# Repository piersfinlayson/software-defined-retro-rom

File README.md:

# One ROM

**One ROM To Rule Them All**

The most flexible ROM replacement for your retro computer. It is highly configurable and low-cost.  Get them fabbed at JLC for under $5 each in a quantity of 10 or more.

Based on a Raspberry Pi RP2350 or STM32F4 microcontroller.

One ROM emulates any system's 2364, 2332 and 2316 ROMs, with any chip select configuration, and can serve different images to multiple ROM sockets simultaneously.

Replaces failed ROMs in Commodore 64s, VIC-20s, PETs, disk drives.

One ROM was formerly known as Software Defined Retro ROM (SDRR).

## Key Features

💰 Based on sub-$2 microcontrollers.  [**Choose from Raspberry Pi or STM flavours**]((docs/MCU-SELECTION.md)).

⚡ **[Fast](docs/STM32-SELECTION.md)** enough for PETs, VIC-20s, C64s, 1541s, IEEE drives, etc. Support faster systems with higher end microcontroller.

📐 **[Same footprint](docs/images/sdrr-24-pin-side.png)** as original ROMs - doesn't overhang the socket like other solutions.

🚀 **[Quick programming](docs/PROGRAMMING.md)** - just connect 4 wires and `make run`. No programming jigs necessary.

🔌 **[Use a $5 programmer](docs/PI-PICO-PROGRAMMER.md)** - no expensive EEPROM programmer required.

🛠️ **[Reflash in situ](docs/PROGRAMMING.md)** - no need to remove the ROM from the host when reprogramming.

⚙️ **[Software configurable](docs/CONFIGURATION.md)** chip select lines - no hardware jumpers required.

💾 Stores up to **[16 ROM images](docs/STM32-SELECTION.md)** of different sizes and chip select configurations.  Image selectable via jumpers.

📦 **[Replace multiple ROMs with one ROM](docs/MULTI-ROM-SETS.md)** a single One ROM can replace up to 3 original ROMs e.g. all of C64 kernel, BASIC, character set.

🔀 **[Dynamic bank switching](docs/MULTI-ROM-SETS.md)** - switch between ROM images on the fly, e.g. different char ROMs.

💻 **[Hackable at runtime](docs/RUNTIME-ACCESS.md)** - change the ROM images being served and access telemetry from the ROM at runtime using **[Airfrog](https://piers.rocks/u/airfrog)** or other SWD probes.

🧩 **[Images combined automatically](docs/CONFIGURATION.md)** - no need to manually build up your own larger PROM image containing multiple retro ROMs.

🏭 **[Two layer PCB](sdrr-pcb/README.md)**, component on single-side, limited BOM for low manufacturing cost/complexity.

🎯 Supports multiple **[STM32F4xxR](docs/STM32-SELECTION.md)** variants: F401, F411, F405, F446 (others can be added).

🔓 **[Open source](LICENSE.md)** software and hardware.

## Introduction

The video below provides an introduction to One ROM:

## Hardware

This is the RP2350 24-pin version, hardware revison A.  See [sdrr-pcb](sdrr-pcb/README.md) for the hardware designs and documentation.

<div style="display: flex; justify-content: center; gap: 20px;">
  
</div>

## Quick Start

You have two options

- [use the pre-built binaries](#pre-built-binaries)
- [build the firmware yourself.](#build-yourself)

### Pre-built Binaries

Use [Airfrog](https://piers.rocks/u/airfrog) or your favourite STM32 programmer to flash the pre-built binaries from the project's [releases](https://github.com/piersfinlayson/software-defined-retro-rom/releases/) page.  Scroll down to the "Assets" section of the latest release, and download the `bin-*.zip` or `elf-*.zip` file for your STM32 variant.  These zip files contain pre-built binaries for the various One ROM image collections, including the C64, VIC-20, PET, and 1541 disk drive.

### Build Yourself

Once you have the project cloned, and the required [dependencies](INSTALL.md) installed, you can build and flash an One ROM image using the following commands - replace `f411re` with your [target MCU variant](docs/MCU-SELECTION.md), and [`config/c64.mk`](/config/c64.mk) with the [configuration](config/README.md#available-configurations) you want to use.

```bash
# C64 using RP2350
HW_REV=p24-a MCU=rp2350 CONFIG=config/c64.mk make run
```

```bash
# C64 using F411RE
MCU=f411re CONFIG=config/c64.mk make run
```

```bash
# VIC-20 (PAL) using F411RE
MCU=f411re CONFIG=config/vic20-pal.mk make run
```

```bash
# PET 40 column 50Hz using F411RE
MCU=f411re CONFIG=config/pet-4-40-50.mk make run
```

This will download the desired ROM images automatically, generate the required firmware, and flash it to One ROM.

### After Flashing

Set the [One ROM jumpers](docs/IMAGE-SELECTION.md) to select the desired ROM image (see the [config file](/config/), or logs from your One ROM device, for which # corresponds to which image) and you're now ready to install the One ROM device in your retro system.

For configuration options, see [Configuration](docs/CONFIGURATION.md) and the [Makefile](Makefile).

## Documentation

| Topic | Description |
|-------|-------------|
| [Frequently Asked Questions](docs/FAQ.md) | Answers to common questions about One ROM. |
| [Installation](INSTALL.md) | Installation of dependencies. |
| [Programming](docs/PROGRAMMING.md) | How to program One ROM. |
| [Available Configurations](config/README.md#available-configurations) | Various pre-collated ROM collection configurations. |
| [MCU Selection](docs/MCU-SELECTION.md) | How to select the appropriate MCU for your application. |
| [Image Selection](docs/IMAGE-SELECTION.md) | How to tell One ROM which of the installed ROM images to serve. |
| [Image Sets](docs/MULTI-ROM-SETS.md) | How to use a single One ROM to support multiple ROMs simultaneously or to dynamically switch between images. |
| [Configuration](docs/CONFIGURATION.md) | One ROM configuration options. |
| [Runtime Access/Control](docs/RUNTIME-ACCESS.md) | Access and control the One ROM while it is serving ROMs. |
| [Compatibility](docs/COMPATIBILITY.md) | Compatibility with various retro systems. |
| [Logging](docs/LOGGING.md) | How to enable and use One ROM logging. |
| [Technical Summary](docs/TECHNICAL-SUMMARY.md) | Overview of the One ROM architecture, operation and design decisions. |
| [Technical Details](docs/TECHNICAL-DETAILS.md) | Technical details of the One ROM firmware and hardware. |
| [Custom Hardware](docs/CUSTOM-HARDWARE.md) | Guide on designing custom hardware for One ROM. |
| [Build System](docs/BUILD-SYSTEM.md) | How the One ROM build system works. |
| [Voltage Levels](docs/VOLTAGE-LEVELS.md) | How the One ROM supports the required logic voltage levels. |
| [Pi Pico Programmer](docs/PI-PICO-PROGRAMMER.md) | How to use a $5 Raspberry Pi Pico as a programmer for One ROM. |
| [Manufacturing Test](docs/MANUFACTURING-TEST.md) | Information on testing One ROM during manufacturing. |
| [STM32 Clones](docs/STM32-CLONES.md) | Information using STM32 clones with One ROM. |
| [Future Enhancements](docs/FUTURE-ENHANCEMENTS.md) | Possible future enhancements under consideration. |
| [License](LICENSE.md) | One ROM software and hardware licenses. |

## Debugging

The best place to start with debugging is [`Logging`](docs/LOGGING.md).  This will help you see what the One ROM is doing, and why it may not be working as expected.

If you have an [Airfrog](https://piers.rocks/u/airfrog), you can use it to inspect the One ROM firmware and its current state.

If you'd like a hand, raise an issue on the [GitHub issues page](https://github.com/piersfinlayson/software-defined-retro-rom/issues).  Please provide:

- the MCU you are using and the PCB type/revision
- the retro system you are trying to One ROM with
- any logging from One ROM
- ideally, the firmware image, if you are happy to share.

If you have built the firmware yourself, rather than using a pre-built release image, also provide:

- your build configuration
- the output from `make info-detail`.

## License

See [LICENSE](LICENSE.md) for software and hardware licensing information.

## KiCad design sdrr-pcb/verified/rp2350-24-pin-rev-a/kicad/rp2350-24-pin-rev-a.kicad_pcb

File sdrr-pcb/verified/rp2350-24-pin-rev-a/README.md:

# RP2350 24 Pin Rev A

23xx (RP2350 24 pin) ROM replacement SDRR PCB.

**Verified** - The BOM/CPL files have been verified using JLCPCB.  However, you should always check the gerbers, component lists and component orientations with your supplier before ordering.

This is the first RP2350 revision, supported by v0.4.0 of the firmware.  While testing of all main features has been performed, this hardware design is less mature than the STM32F4 designs.

<div style="text-align: center;">
  
</div>

## Contents

- [Schematic](one-rom-24-pin-rp2350-rev-a-schematic.pdf)
- [Fab Notes](one-rom-24-pin-rp2350-rev-a-fab-notes.pdf)
- [Fab Files](fab/)
- [KiCad Design Files](kicad/)
- [Errata](#errata)
- [Notes](#notes)
- [Changelog](#changelog)

## Errata

None

## Notes

None

## Changelog

First revison

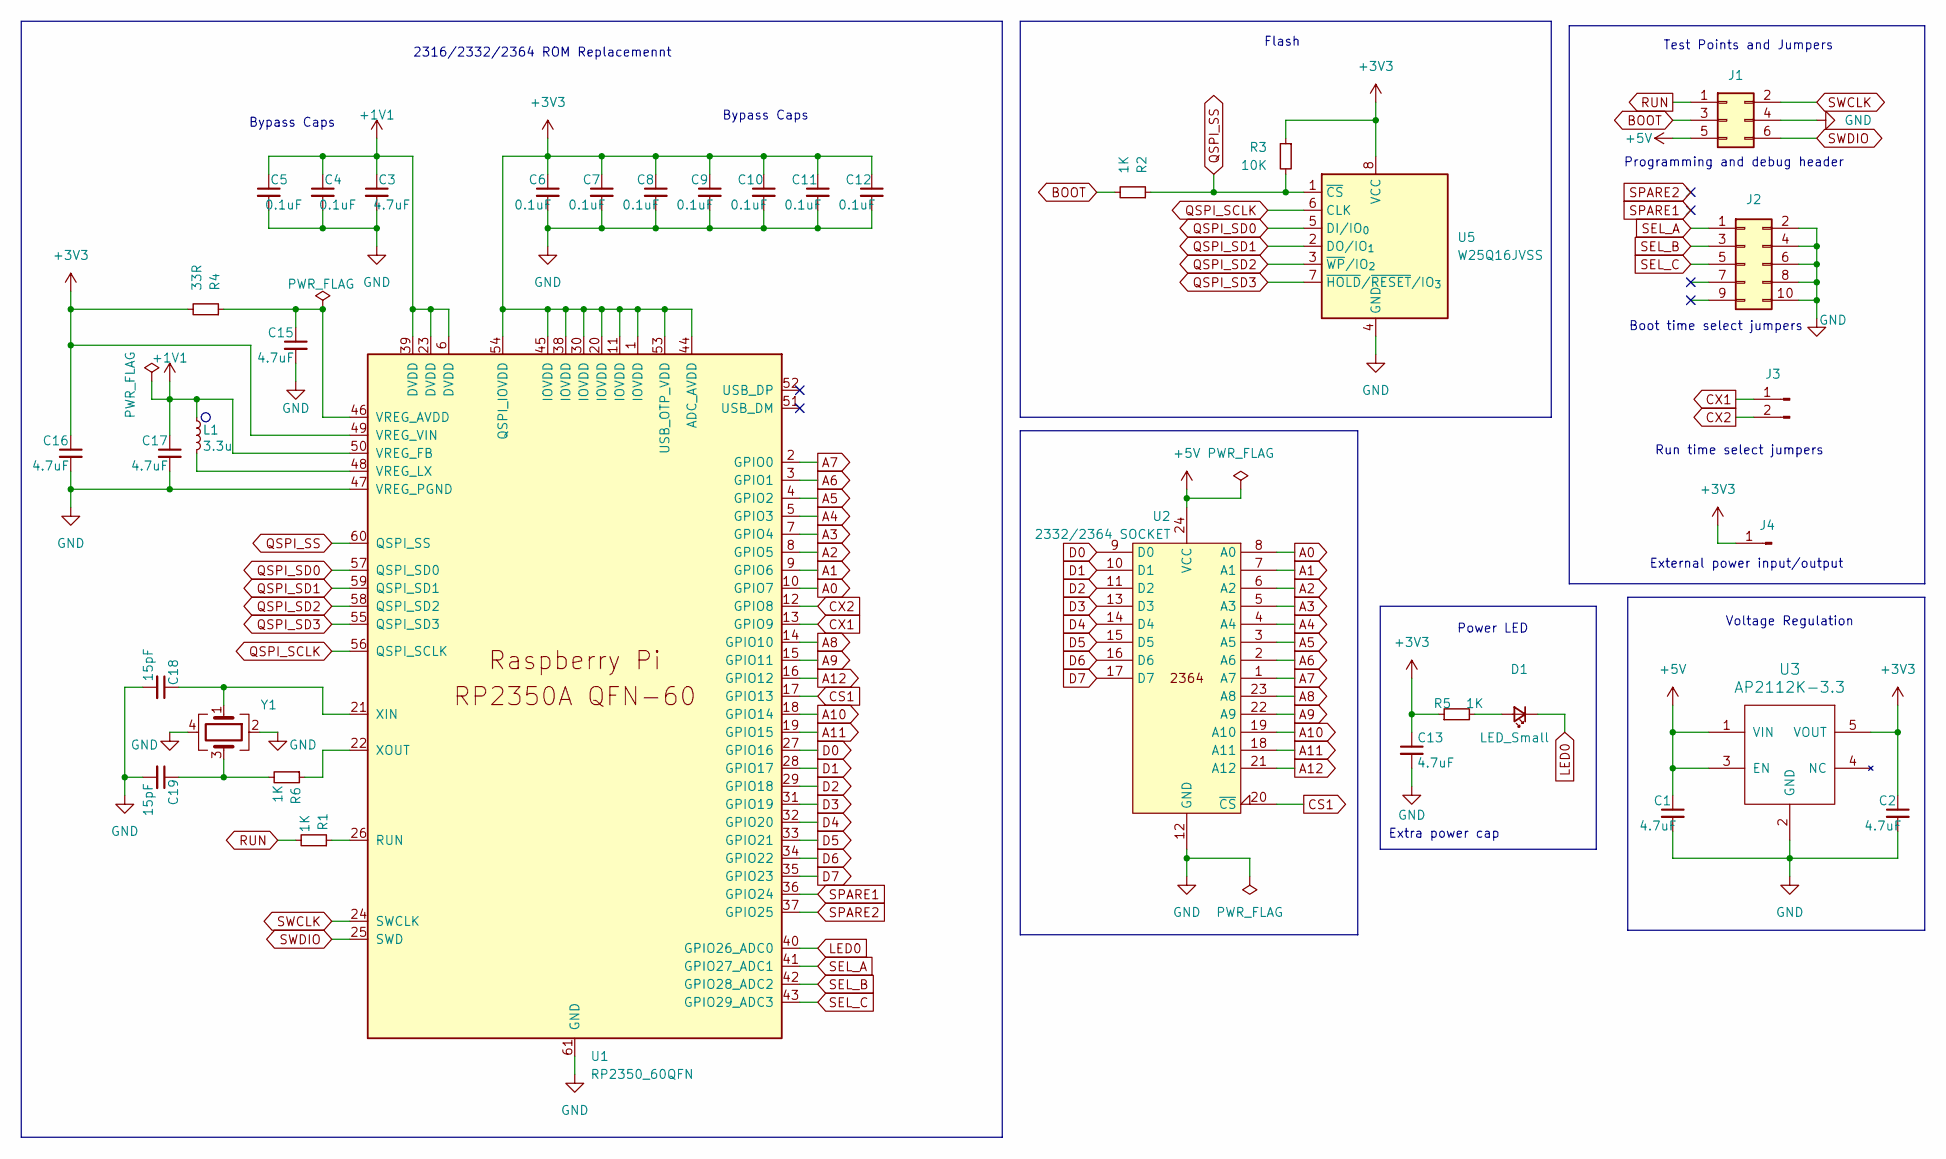
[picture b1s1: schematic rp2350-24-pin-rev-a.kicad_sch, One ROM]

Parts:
C1, C2, C3, C13, C15: 4.7uF; C_0402_1005Metric; LCSC C23733
C4, C5, C6, C7, C8, C9, C10, C11, C12: 0.1uF; C_0402_1005Metric; LCSC C1525
C16, C17: 4.7uF; C_0402_1005Metric_small_pads; LCSC C23733
C18, C19: 15pF; C_0402_1005Metric; LCSC C1548
D1: LED_Small; LED_0603_1608Metric; LCSC C2286
J1: Conn_02x03_Odd_Even; PinHeader_2x03_P2.54mm_Vertical
J2: Conn_02x05_Odd_Even; PinHeader_2x05_P2.54mm_Vertical custom silkscreen
J3: Conn_01x02_Pin; PinHeader_1x02_P2.54mm_Vertical
J4: Conn_01x01_Pin; PinHeader_1x01_P2.54mm_Vertical
L1: 3.3u; L_pol_2016; LCSC C42411119
R1, R2, R5, R6: 1K; R_0402_1005Metric; LCSC C11702
R3: 10K; R_0402_1005Metric; LCSC C25744
R4: 33R; R_0402_1005Metric; LCSC C25105
U1: RP2350_60QFN; RP2350-QFN-60-1EP_7x7_P0.4mm_EP3.4x3.4mm_ThermalVias; LCSC C42411118
U2: 2332/2364 SOCKET; 2x12 dip pin output 600mil centres no ss
U3: AP2112K-3.3; SOT-23-5; LCSC C51118
U5: W25Q16JVSS; Winbond_USON-8-1EP_3x2mm_P0.5mm_EP0.2x1.6mm; LCSC C2843335
Y1: Crystal_GND24; Crystal_SMD_Abracon_ABM8G-4Pin_3.2x2.5mm; LCSC C20625731

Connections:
+1V1: C3.1, C4.1, C5.1, C17.1, L1.1, U1.6 (DVDD), U1.23 (DVDD), U1.39 (DVDD), U1.50 (VREG_FB)
+3V3: C2.1, C6.1, C7.1, C8.1, C9.1, C10.1, C11.1, C12.1, C13.1, C16.1, J4.1, R3.1, R4.2, R5.1, U1.1 (IOVDD), U1.11 (IOVDD), U1.20 (IOVDD), U1.30 (IOVDD), U1.38 (IOVDD), U1.44 (ADC_AVDD), U1.45 (IOVDD), U1.49 (VREG_VIN), U1.53 (USB_OTP_VDD), U1.54 (QSPI_IOVDD), U3.5 (VOUT), U5.8 (VCC)
+5V: C1.1, J1.5, U2.24 (VCC), U3.1 (VIN), U3.3 (EN)
A0: U1.10 (GPIO7), U2.8 (A0)
A1: U1.9 (GPIO6), U2.7 (A1)
A2: U1.8 (GPIO5), U2.6 (A2)
A3: U1.7 (GPIO4), U2.5 (A3)
A4: U1.5 (GPIO3), U2.4 (A4)
A5: U1.4 (GPIO2), U2.3 (A5)
A6: U1.3 (GPIO1), U2.2 (A6)
A7: U1.2 (GPIO0), U2.1 (A7)
A8: U1.14 (GPIO10), U2.23 (A8)
A9: U1.15 (GPIO11), U2.22 (A9)
A10: U1.18 (GPIO14), U2.19 (A10)
A11: U1.19 (GPIO15), U2.18 (A11)
A12: U1.16 (GPIO12), U2.21 (A12)
BOOT: J1.3, R2.2
CS1: U1.17 (GPIO13), U2.20 (~CS)
CX1: J3.1, U1.13 (GPIO9)
CX2: J3.2, U1.12 (GPIO8)
D0: U1.27 (GPIO16), U2.9 (D0)
D1: U1.28 (GPIO17), U2.10 (D1)
D2: U1.29 (GPIO18), U2.11 (D2)
D3: U1.31 (GPIO19), U2.13 (D3)
D4: U1.32 (GPIO20), U2.14 (D4)
D5: U1.33 (GPIO21), U2.15 (D5)
D6: U1.34 (GPIO22), U2.16 (D6)
D7: U1.35 (GPIO23), U2.17 (D7)
GND: C1.2, C2.2, C3.2, C4.2, C5.2, C6.2, C7.2, C8.2, C9.2, C10.2, C11.2, C12.2, C13.2, C15.2, C16.2, C17.2, C18.2, C19.2, J1.4, J2.2, J2.4, J2.6, J2.8, J2.10, U1.47 (VREG_PGND), U1.61 (GND), U2.12 (GND), U3.2 (GND), U5.4 (GND), Y1.2, Y1.4
LED0: D1.1 (K), U1.40 (GPIO26_ADC0)
unnamed: C19.1, R6.2, Y1.3
unnamed: D1.2 (A), R5.2
unnamed: R1.1, U1.26 (RUN)
unnamed: C15.1, R4.1, U1.46 (VREG_AVDD)
unnamed: L1.2, U1.48 (VREG_LX)
unnamed: C18.1, U1.21 (XIN), Y1.1
unnamed: R6.1, U1.22 (XOUT)
QSPI_SCLK: U1.56 (QSPI_SCLK), U5.6 (CLK)
QSPI_SD0: U1.57 (QSPI_SD0), U5.5 (DI/IO_{0})
QSPI_SD1: U1.59 (QSPI_SD1), U5.2 (DO/IO_{1})
QSPI_SD2: U1.58 (QSPI_SD2), U5.3 (~WP/IO_{2})
QSPI_SD3: U1.55 (QSPI_SD3), U5.7 (~HOLD/~RESET/IO_{3})
QSPI_SS: R2.1, R3.2, U1.60 (QSPI_SS), U5.1 (~CS)
RUN: J1.1, R1.2
SEL_A: J2.1, U1.41 (GPIO27_ADC1)
SEL_B: J2.3, U1.42 (GPIO28_ADC2)
SEL_C: J2.5, U1.43 (GPIO29_ADC3)
SPARE1: U1.36 (GPIO24)
SPARE2: U1.37 (GPIO25)
SWCLK: J1.2, U1.24 (SWCLK)
SWDIO: J1.6, U1.25 (SWD)

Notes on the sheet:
Run time select jumpers
Voltage Regulation
Extra power cap
2316/2332/2364 ROM Replacemennt
Bypass Caps
Power LED
Programming and debug header
External power input/output
Flash
Boot time select jumpers
Test Points and Jumpers

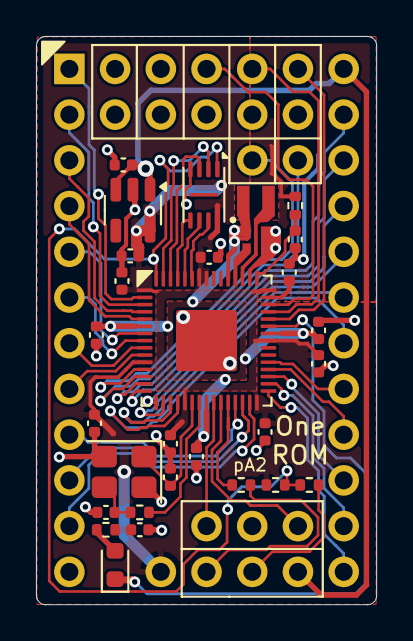
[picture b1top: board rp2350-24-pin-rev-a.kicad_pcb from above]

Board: 2 copper layers, 18.9 x 31.6 mm, 35 parts (0 on the bottom side), 49 nets.

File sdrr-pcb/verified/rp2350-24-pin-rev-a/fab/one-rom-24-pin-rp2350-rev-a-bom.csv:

"Reference","Value","Qty","DNP","LCSC","Comment","Price(10)"
"C1,C2,C3,C13,C15,C16,C17","4.7uF","7","","C23733","Samsung Electro-Mechanics CL05A475MP5NRNC","$0.0048"
"C4,C5,C6,C7,C8,C9,C10,C11,C12","0.1uF","9","","C1525","Samsung Electro-Mechanics CL05B104KO5NNNC","$0.0011"
"C18,C19","15pF","2","","C1548","FH (Guangdong Fenghua Advanced Tech) 0402CG150J500NT","$0.0010"
"D1","LED_Small","1","","C2286","Hubei KENTO Elec KT-0603R","$0.0056"
"L1","3.3u","1","","C42411119","Abracon LLC AOTA-B201610S3R3-101-T","$0.2736"
"R1,R2,R5,R6","1K","4","","C11702","UNI-ROYAL(Uniroyal Elec) 0402WGF1001TCE","$0.0005"
"R3","10K","1","","C25744","UNI-ROYAL(Uniroyal Elec) 0402WGF1002TCE","$0.0005"
"R4","33R","1","","C25105","UNI-ROYAL(Uniroyal Elec) 0402WGF330JTCE","$0.0006"
"U1","RP2350_60QFN","1","","C42411118","Raspberry Pi RP2350A","$1.4430"
"U3","AP2112K-3.3","1","","C51118","Diodes Incorporated AP2112K-3.3TRG1","$0.1059"
"U5","W25Q16JVSS","1","","C2843335","Winbond Elec W25Q16JVUXIQ","$0.5220"
"Y1","Crystal_GND24","1","","C20625731","Abracon LLC ABM8-272-T3","$0.4200"

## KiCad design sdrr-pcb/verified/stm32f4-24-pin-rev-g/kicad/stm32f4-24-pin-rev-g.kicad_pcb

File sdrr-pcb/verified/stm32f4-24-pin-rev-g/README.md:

# STM32F4 24 Pin Rev G

One ROM 23xx (STM32F4 24 pin) ROM replacement PCB.

**Partially Verified**: Has been verified with STM32F411.  Has not been verified with STM32F405 (although electrically very similar to rev F so highly likely to work).

Electrically similar to the [STM32F4 24 Pin Rev F2](../../verified/stm32f4-24-pin-rev-f2/README.md) board, but with some minor changes to layout:
- A new 2x3 programming header is on the bottom of the PCB - between pins 12 and 13.  This provides compatibility with the 1x3 SWD header on the Pico/Pico 2s.
  - As part of this BOOT0 has been moved to this header.
- A 5th image select jumper has been added to the top of the PCB, in plact of BOOT0. It is expected that this wil be used for other purposes other than image selection - such as host reset line, driven by an attached co-processor, such as Airfrog.
- The 5 image select jumpers have been relaballed A-E, and in the reverse order to the F2 board - with the intent that the least significant bit is now on the right.
- Closing the jumpers now pulls the image select line low, rather than high.  This is to expose GND rather than 3V3 on the unconnected pin, which is safer.
- An additional 3V3 and GND pair of pins has been added below X1/X2.  This can be used to power the board for progamming, instead of 5V on the programming header, or to tap a 3V3 source from the on-board regulator.  Care should be taken not to overload this.
- An additional single 3V3 pin has been added to the left of the programming header, for similar reasons.
- The MCO1 (optional clock output) test point has been moved to the underside of the PCB, and is now labelled TP1.
- The status LED has been moved to to next to the programming header, to avoid a daughterboard obscuring it.
- Moved to 0402 passives, with the expectation that most people will use an assembly service, and with a microscope and a decent iron, 0402 is also hand solderable.

There is a single set of gerbers, one CPL/POS file and multiple BOM files, one for each of the followingF4xx microcontrollers, in ascending order of cost:
- STM32F401RET6
- STM32F411RET6
- GD32F405RGT6
- STM32F405RGT6
- STM32F446RET6

<div style="text-align: center;">
  
</div>

## Contents

- [Schematic](sdrr-24-pin-rev-g1-schematic.pdf)
- [Fab Files](fab/) - unverified
- [KiCad Design Files](kicad/)
- [Errata](#errata)
- [Notes](#notes)
- [Changelog](#changelog)
- [BOM](#bom)

## Errata

## Notes

## Changelog

See above

## BOM

See fab files.

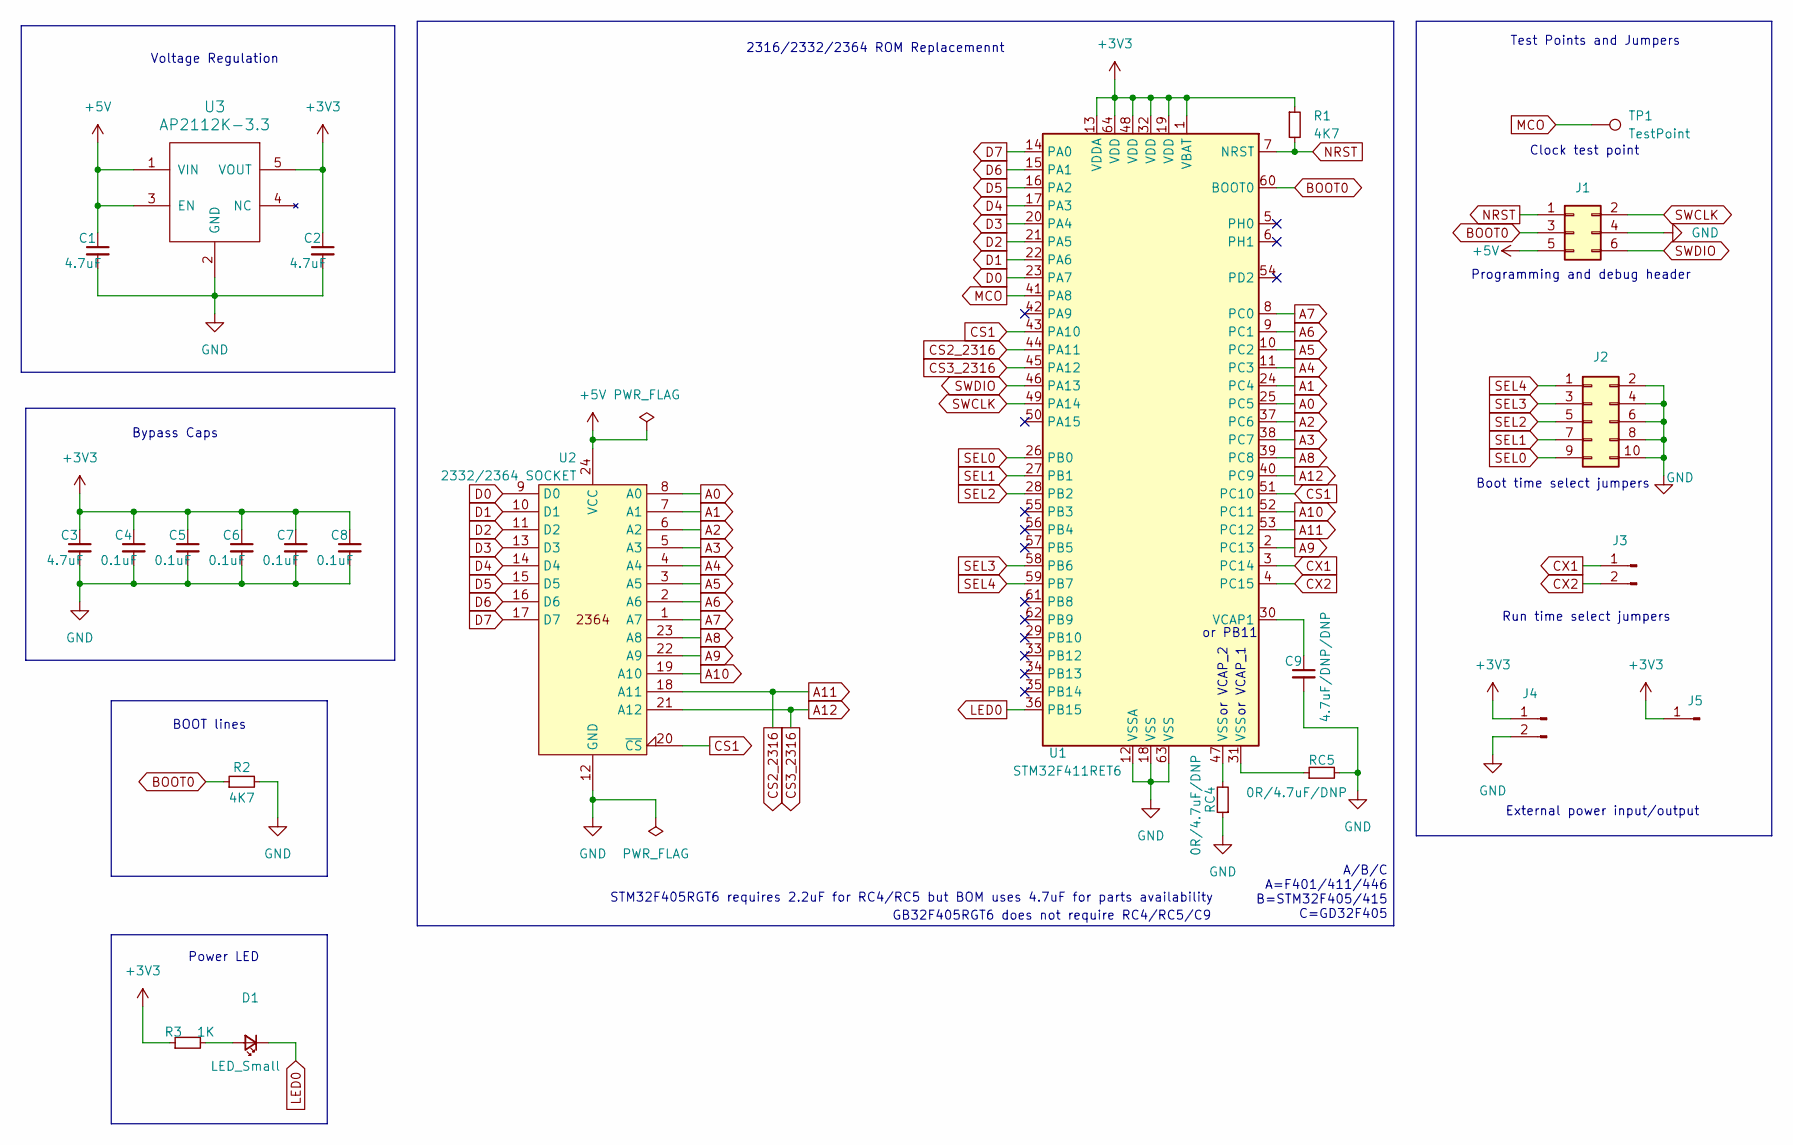
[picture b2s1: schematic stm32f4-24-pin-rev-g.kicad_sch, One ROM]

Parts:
C1, C2, C3: 4.7uF; C_0402_1005Metric; LCSC C23733
C4, C5, C6, C7, C8: 0.1uF; C_0402_1005Metric; LCSC C1525
C9: 4.7uF/DNP/DNP; C_0402_1005Metric; LCSC C23733
D1: LED_Small; LED_0603_1608Metric; LCSC C2286
J1: Conn_02x03_Odd_Even; PinHeader_2x03_P2.54mm_Vertical
J2: Conn_02x05_Odd_Even; PinHeader_2x05_P2.54mm_Vertical custom silkscreen
J3: Conn_01x02_Pin; PinHeader_1x02_P2.54mm_Vertical
J4: Conn_01x02_Pin; 1x2 pin header no ss, both round, small courtyard
J5: Conn_01x01_Pin; PinHeader_1x01_P2.54mm_Vertical
R1, R2: 4K7; R_0402_1005Metric; LCSC C25900
R3: 1K; R_0402_1005Metric; LCSC C11702
RC4, RC5: 0R/4.7uF/DNP; C_0402_1005Metric; LCSC C17168
TP1: TestPoint; TestPoint_THTPad_1.0x1.0mm_Drill0.5mm
U1: STM32F411RET6; LQFP-64_10x10mm_P0.5mm; LCSC C94355
U2: 2332/2364 SOCKET; 2x12 dip pin output 600mil centres no ss
U3: AP2112K-3.3; SOT-23-5; LCSC C51118

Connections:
+3V3: C2.1, C3.1, C4.1, C5.1, C6.1, C7.1, C8.1, J4.1, J5.1, R1.1, R3.1, U1.1 (VBAT), U1.13 (VDDA), U1.19 (VDD), U1.32 (VDD), U1.48 (VDD), U1.64 (VDD), U3.5 (VOUT)
+5V: C1.1, J1.5, U2.24 (VCC), U3.1 (VIN), U3.3 (EN)
A0: U1.25 (PC5), U2.8 (A0)
A1: U1.24 (PC4), U2.7 (A1)
A2: U1.37 (PC6), U2.6 (A2)
A3: U1.38 (PC7), U2.5 (A3)
A4: U1.11 (PC3), U2.4 (A4)
A5: U1.10 (PC2), U2.3 (A5)
A6: U1.9 (PC1), U2.2 (A6)
A7: U1.8 (PC0), U2.1 (A7)
A8: U1.39 (PC8), U2.23 (A8)
A9: U1.2 (PC13), U2.22 (A9)
A10: U1.52 (PC11), U2.19 (A10)
A11: U1.44 (PA11), U1.53 (PC12), U2.18 (A11)
A12: U1.40 (PC9), U1.45 (PA12), U2.21 (A12)
BOOT0: J1.3, R2.1, U1.60 (BOOT0)
CS1: U1.43 (PA10), U1.51 (PC10), U2.20 (~CS)
CX1: J3.1, U1.3 (PC14)
CX2: J3.2, U1.4 (PC15)
D0: U1.23 (PA7), U2.9 (D0)
D1: U1.22 (PA6), U2.10 (D1)
D2: U1.21 (PA5), U2.11 (D2)
D3: U1.20 (PA4), U2.13 (D3)
D4: U1.17 (PA3), U2.14 (D4)
D5: U1.16 (PA2), U2.15 (D5)
D6: U1.15 (PA1), U2.16 (D6)
D7: U1.14 (PA0), U2.17 (D7)
GND: C1.2, C2.2, C3.2, C4.2, C5.2, C6.2, C7.2, C8.2, C9.2, J1.4, J2.2, J2.4, J2.6, J2.8, J2.10, J4.2, R2.2, RC4.1, RC5.2, U1.12 (VSSA), U1.18 (VSS), U1.63 (VSS), U2.12 (GND), U3.2 (GND)
LED0: D1.1 (K), U1.36 (PB15)
MCO: TP1.1, U1.41 (PA8)
NRST: J1.1, R1.2, U1.7 (NRST)
unnamed: D1.2 (A), R3.2
unnamed: RC4.2, U1.47 (VSS)
unnamed: RC5.1, U1.31 (VSS)
unnamed: C9.1, U1.30 (VCAP1)
SEL0: J2.9, U1.26 (PB0)
SEL1: J2.7, U1.27 (PB1)
SEL2: J2.5, U1.28 (PB2)
SEL3: J2.3, U1.58 (PB6)
SEL4: J2.1, U1.59 (PB7)
SWCLK: J1.2, U1.49 (PA14)
SWDIO: J1.6, U1.46 (PA13)

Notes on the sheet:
or VCAP_1
or VCAP_2
Run time select jumpers
BOOT lines
Voltage Regulation
2316/2332/2364 ROM Replacemennt
Power LED
or PB11
GB32F405RGT6 does not require RC4/RC5/C9
Clock test point
Bypass Caps
Programming and debug header
External power input/output
Boot time select jumpers
A/B/C A=F401/411/446 B=STM32F405/415 C=GD32F405
Test Points and Jumpers
STM32F405RGT6 requires 2.2uF for RC4/RC5 but BOM uses 4.7uF for parts availability

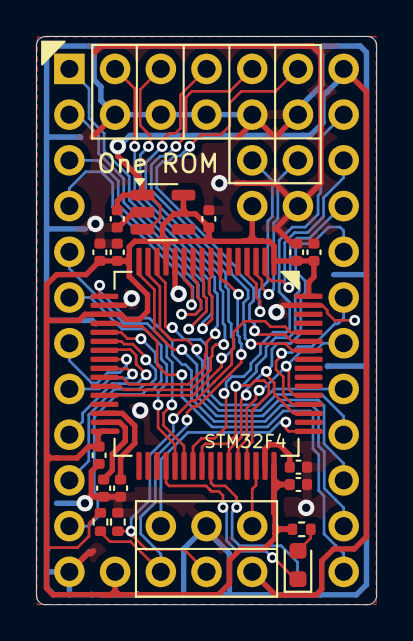
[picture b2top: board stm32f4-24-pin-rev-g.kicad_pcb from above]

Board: 2 copper layers, 18.9 x 31.6 mm, 24 parts (1 on the bottom side), 42 nets.

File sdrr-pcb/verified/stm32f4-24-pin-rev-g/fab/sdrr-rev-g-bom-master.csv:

"Reference","Value","Qty","LCSC"
"C1,C2,C3","4.7uF","3","C23733"
"C4,C5,C6,C7,C8","0.1uF","5","C1525"
"C9","4.7uF/DNP/DNP","1","C23733"
"D1","LED_Small","1","C2286"
"J1","Conn_02x03_Odd_Even","1",""
"J2","Conn_02x05_Odd_Even","1",""
"J3,J4","Conn_01x02_Pin","2",""
"J5","Conn_01x01_Pin","1",""
"R1,R2","4K7","2","C25900"
"R3","1K","1","C11702"
"RC4,RC5","0R/4.7uF/DNP","2","C17168"
"TP1","TestPoint","1",""
"U1","STM32F4xx","1","C94355"
"U2","2332/2364 SOCKET","1",""
"U3","AP2112K-3.3","1","C51118"

# F411RE
"Reference","Value","Qty","LCSC"
"C1,C2,C3","4.7uF","3","C23733"
"C4,C5,C6,C7,C8","0.1uF","5","C1525"
"C9","4.7uF","1","C23733"
"D1","LED_Small","1","C2286"
"R1,R2","4K7","2","C25900"
"R3","1K","1","C11702"
"RC4,RC5","0R/4.7uF/DNP","2","C17168"
"U1","STM32F4xx","1","C94355"
"U3","AP2112K-3.3","1","C51118"

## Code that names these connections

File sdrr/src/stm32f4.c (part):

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    //
    uint32_t gpioa_moder = 0;
    uint32_t gpioa_pupdr = 0;
    uint32_t gpioa_ospeedr = 0x0000AAAA;    // PA0-7 fast speed, not high
                                            // speed, to ensure V(OL) max 0.4V

    if (sdrr_info.swd_enabled) {
        gpioa_moder |= 0x28000000; // Set 13/14 as AF
        gpioa_pupdr |= 0x24000000; // Set pull-up on PA13, down on PA14
    }

    if (sdrr_info.mco_enabled) {
        gpioa_moder |= 0x00020000; // Set PA8 as AF
        gpioa_ospeedr |= 0x00030000; // Set PA8 to very high speed
    }
    
    GPIOA_MODER = gpioa_moder;
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    // GPIOB and GPIOC
    //

    // Set PB0-2 and PB7 as inputs, with pull-downs.  HW rev D only uses
    // PB0-2 but as PB7 isn't connected we can set it here as well.
    // We do this early doors, so the internal pull-downs will have settled
    // before we read the pins.
    // TODO the code to set PU/PD should be retired (and then tested as the
    // PU/PD is now done in check_sel_pins()).
    GPIOB_MODER = 0;  // Set all GPIOs as inputs
    GPIOB_PUPDR &= ~0x0000C03F;  // Clear pull-up/down for PB0-2 and PB7
    GPIOB_PUPDR |= 0x0000802A;   // Set pull-downs on PB0-2 and PB7

    GPIOC_MODER = 0;  // Set all GPIOs as inputs

#if defined(MCO2)
    uint32_t gpioc_moder = GPIOC_MODER;
    gpioc_moder &= ~(0b11 << (9 * 2));  // Clear bits for PC9
    gpioc_moder |= 0x00080000; // Set PC9 as AF
    GPIOC_MODER = gpioc_moder;
    GPIOC_OSPEEDR |= 0x000C0000; // Set PC9 to very high speed
    GPIOC_OTYPER &= ~(0b1 << 9);  // Set as push-pull
#else // !MCO2
    GPIOC_PUPDR = 0; // No pull-up/down
#endif // MCO2
}

// Common setup for status LED output using PB15 (inverted logic: 0=on, 1=off)
void setup_status_led(void) {
    if (sdrr_info.pins->status_port != PORT_B) {
        LOG("!!! Status port not B - not using");
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        RCC_AHB1ENR |= RCC_AHB1ENR_GPIOBEN; // Enable GPIOB clock
        
        uint8_t pin = sdrr_info.pins->status;
        GPIOB_MODER &= ~(0x3 << (pin * 2));  // Clear bits for PB15
        GPIOB_MODER |= (0x1 << (pin * 2));   // Set as output
        GPIOB_OSPEEDR |= (0x3 << (pin * 2)); // Set speed to high speed
        GPIOB_OTYPER &= ~(0x1 << pin);       // Set as push-pull
        GPIOB_PUPDR &= ~(0x3 << (pin * 2));  // No pull-up/down
        
        GPIOB_BSRR = (1 << pin); // Start with LED off (PB15 high)
    }
}

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#endif // HSI_TRIM
    LOG("PLL MNPQ: %d/%d/%d/%d", PLL_M, PLL_N, PLL_P, PLL_Q);
    if (sdrr_info.mco_enabled) {
        LOG("MCO: enabled - PA8");
    } else {
        LOG("MCO: disabled");
    }
#if defined(MCO2)
    LOG("MCO2: %s - PC9", enabled);
#endif // MCO2

#endif // BOOT_LOGGING
}

// Sets up the MCO (clock output) on PA8, to the value provided
void setup_mco(void) {
    uint8_t mco = RCC_CFGR_MCO1_PLL;

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    RCC_AHB1ENR |= (1 << 0);

    uint32_t gpioa_moder = GPIOA_MODER;
    gpioa_moder &= ~(0b11 << (8 * 2));  // Clear bits for PA8
    gpioa_moder |= (0b10 << (8 * 2));   // Set as AF
    GPIOA_MODER = gpioa_moder;
    GPIOA_OSPEEDR |= (0b11 << (8 * 2));  // Set speed to very high speed
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
#if defined(MCO2)
    uint32_t gpioc_moder = GPIOC_MODER;
    gpioc_moder &= ~(0b11 << (9 * 2));  // Clear bits for PC9
    gpioc_moder |= (0b10 << (9 * 2));   // Set as AF
    GPIOC_MODER = gpioc_moder;
    GPIOC_OSPEEDR |= (0b11 << (9 * 2));  // Set speed to very high speed
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
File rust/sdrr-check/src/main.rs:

// Copyright (c) 2025 Piers Finlayson <piers@piers.rocks>
//
// MIT licence

#![no_std]
#![no_main]
#![feature(type_alias_impl_trait)]

#[cfg(not(feature = "hw-24-f"))]
compile_error!("Only hardware revision 24-f currently supported");

#[allow(unused_imports)]
use defmt::{debug, error, info, trace, warn};
use defmt_rtt as _;
use embassy_executor::Spawner;
use embassy_executor::main as embassy_main;
use embassy_stm32::exti::ExtiInput;
use embassy_stm32::gpio::{Level, Output, Pull, Speed};
use embassy_time::{Duration, Timer};
use panic_probe as _;

const LED_FLASH_INTERVAL: Duration = Duration::from_millis(500);

// Our main entry point.
#[embassy_main]
async fn main(spawner: Spawner) {
    let p = embassy_stm32::init(Default::default());

    debug!("Spawning jumper detection tasks");
    let j1 = ExtiInput::new(p.PB0, p.EXTI0, Pull::Down);
    let j2 = ExtiInput::new(p.PB1, p.EXTI1, Pull::Down);
    let j4 = ExtiInput::new(p.PB2, p.EXTI2, Pull::Down);
    let j8 = ExtiInput::new(p.PB7, p.EXTI7, Pull::Down);
    let x1 = ExtiInput::new(p.PC14, p.EXTI14, Pull::Down);
    let x2 = ExtiInput::new(p.PC15, p.EXTI15, Pull::Down);

    spawner.must_spawn(monitor_pin(j1, "J1"));
    spawner.must_spawn(monitor_pin(j2, "J2"));
    spawner.must_spawn(monitor_pin(j4, "J4"));
    spawner.must_spawn(monitor_pin(j8, "J8"));
    spawner.must_spawn(monitor_pin(x1, "X1"));
    spawner.must_spawn(monitor_pin(x2, "X2"));

    // Set up the LED flashing task
    debug!("Spawning LED flash task");
    let led_pin = Output::new(p.PB15, Level::High, Speed::Medium);
    spawner.must_spawn(flash_led_task(led_pin));

    info!("SDRR Check started");
    info!("- Status LED (if installed to PB15) should be flashing");
    info!("- Open/Close jumpers 1/2/4/8 and X1/X2 and check logs");
    loop {
        Timer::after(Duration::from_secs(1)).await;
    }
}

#[embassy_executor::task(pool_size = 6)]
async fn monitor_pin(mut pin: ExtiInput<'static>, name: &'static str) {
    let mut last_state = pin.is_high();

    loop {
        pin.wait_for_any_edge().await;
        let current_state = pin.is_high();

        if current_state != last_state {
            info!(
                "{} changed: {}",
                name,
                if current_state { "high" } else { "low" }
            );
            last_state = current_state;
        }
    }
}

// A task to flash the status LED
#[embassy_executor::task]
async fn flash_led_task(mut gpio: Output<'static>) -> ! {
    loop {
        // Flash the LED
        gpio.set_high();
        Timer::after(LED_FLASH_INTERVAL).await;

        gpio.set_low();
        Timer::after(LED_FLASH_INTERVAL).await;
    }
}

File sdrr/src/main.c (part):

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}

// Check whether we shoud enter the device's bootloader and, if so, enter it.
// This is indicated via jumping SEL0, SEL1, and SEL2 - PB0-2.  These are all
// pulled up to enter the bootloader.  STM32F4 variant from rev E onwards also
// include PB7 as the most significant bit.
//
// This must be done before we set up the PLL, peripheral clocks, etc, as
// those must be disabled for the bootloader.
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
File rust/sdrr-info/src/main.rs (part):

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            }
            println!();
            println!("Image select pins:");
            if pins.sel0 != 0xFF {
                println!("  SEL0: P{}:{}", pins.sel_port, pins.sel0);
            }
            if pins.sel1 != 0xFF {
                println!("  SEL1: P{}:{}", pins.sel_port, pins.sel1);
            }
            if pins.sel2 != 0xFF {
                println!("  SEL2: P{}:{}", pins.sel_port, pins.sel2);
            }
            if pins.sel3 != 0xFF {
                println!("  SEL3: P{}:{}", pins.sel_port, pins.sel3);
            }
            if pins.sel4 != 0xFF {
                println!("  SEL4: P{}:{}", pins.sel_port, pins.sel4);
            }
            if pins.sel5 != 0xFF {
                println!("  SEL5: P{}:{}", pins.sel_port, pins.sel5);
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
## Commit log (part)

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2025-07-01 move to fast speed outputs and do voltage level analysis
2025-07-01 avoid building when only docs change
2025-07-02 uprev vic20 dead test image
2025-07-02 add video
2025-07-03 add PCB rev e details
2025-07-03 add .pos files, for pick and place machines
2025-07-04 add technical summary
2025-07-04 add F446 support - untested
2025-07-05 add hw revision f
2025-07-05 add 28 pin and wifi prog hw files
2025-07-05 more 2332 thoughts
2025-07-05 add thoughts on multiple rom implementation, rework config types into base config header
2025-07-05 initial implementation of rom sets - currently one image per set
2025-07-06 add serving algorithm for multi rom sets
2025-07-06 auto-gen linker script
2025-07-06 generate linker file
2025-07-06 improve new algorithm perf
2025-07-06 generate properly mangled data for rom sets, and provide a tester
2025-07-07 increase version
2025-07-07 make serving algorithm configurable
2025-07-07 fix log
2025-07-07 fix alg2 main loop - need loop back to start!
2025-07-07 think I have multi-rom sets implemented completely now
2025-07-07 need use to CS_TEST_ANY in set case
2025-07-08 better comments in roms.c
2025-07-08 fix some bugs in cs selection
2025-07-08 fix critical CS_TEST_ANY bug (BICS vs BIC)
2025-07-08 add another set
2025-07-09 create sddr-info and rework #define/config options
2025-07-09 bit of docs on sdrr-info
2025-07-09 add technical dvideo to doc
2025-07-09 make compilable with gcc 11
2025-07-09 fix building with new config_base.h
2025-07-09 add function to sddr-info to lookup bytes from the embedded images
2025-07-09 output binary data to stdout
2025-07-09 add --detail option
2025-07-09 addedmore sdrr-info documentation
2025-07-09 improve builds
2025-07-10 make ports and pins configurable at runtime
2025-07-10 make hw configs configurable using json files
2025-07-10 firmware uses config pins where possible
2025-07-11 use configured pin mappings in sdrr-gen and improve build system
2025-07-11 fix multi rom sets
2025-07-11 improve test option
2025-07-11 get multi-rom sets properly encoding 0xaa for unused portions of the 64KB image
2025-07-12 remove old docs
2025-07-12 add custom firmware doc
2025-07-12 add custom firmware docs
2025-07-12 dynamically load hw config in test
2025-07-12 create common rust library
2025-07-12 handle d, e, f specially
2025-07-12 get rust binaries from correct directory
2025-07-12 get sdrr-info ranges working properly, and dynamic pin assignment
2025-07-12 improve docs
2025-07-12 rename boards
2025-07-13 add MAIN_LOOP_ONE_SHOT
2025-07-13 fix multi-rom sets
2025-07-13 improve logging
2025-07-13 fix sel pins operation
2025-07-13 improve CS logging
2025-07-13 get multi-rom support working with C64#
2025-07-13 change version to 0.2.0
2025-07-13 capture new logs
2025-07-13 add libjson-c-dev to github worklows
2025-07-13 don't build firmware images for sets, as requires hw rev f
2025-07-13 add some more tests for new features
2025-07-13 Release v0.2.0 (#1)
    Main additions:
    - A single SDRR can be used to replace multiple ROM chips simultaneously.
    - New sdrr-info tool to extract details and ROM images from firmware.
    - Add your own hardware configurations, by adding a simple JSON file.
    - New STM32F4 variants supported.
    - Comprehensive testing of compiled in images to ensure veracity.
2025-07-13 include version in makefile output
2025-07-13 add question
2025-07-13 add to comment
2025-07-13 move rust to rust/
2025-07-14 add pull-ups/downs on X1/X2 so still works if some CS lines disconnected
2025-07-14 move assembly to rom_asm.h and macroize more code to reduce the size of the source code
2025-07-14 fix ACT_LOW bugs
2025-07-14 provide user image directory
2025-07-14 update measured min clock speeds, use B as default algorithm
2025-07-14 update changelog
2025-07-14 Improve serving algorithm and update measurements (#3)
    * add pull-ups/downs on X1/X2 so still works if some CS lines disconnected
    * move assembly to rom_asm.h and macroize more code to reduce the size of the source code
    * fix ACT_LOW bugs
    * provide user image directory
    * provide user image directory
    * update measured min clock speeds, use B as default algorithm
2025-07-14 add 1541 set and measurements
2025-07-14 correct blacklist format
2025-07-14 improve stm32 selection docs
2025-07-14 add ID code and hw flash size detection
2025-07-14 add idcode and flash to changelog
2025-07-14 fix debug build, and include flash size check in reguar logging build
2025-07-14 put status LED control is outside of MAIN_LOOP_ONE_SHOT
2025-07-15 correct flash size handling
2025-07-15 don't output STM32 in ID code as may be clone
2025-07-15 remove stm32 as could be built for a clone
2025-07-15 add stm32 clone documentation
2025-07-15 move rev e to verified status
2025-07-15 uprev version to 0.2.1 so builds from main don't show old version
2025-07-15 move firmware parsing into separate crate, use deku, and make no_std compatible
2025-07-15 fix up Makefile
2025-07-15 Move firmware parsing into a separate no_std capable library in preparation for embedding within a programmer (#4)
    * move rust code to new rust/ directory
    * move firmware parsing into separate crate, use deku, and make no_std compatible
    * fix up Makefile
    * merge into other v0.2.1 changes
2025-07-16 initial commit of docker support
2025-07-16 fix docker files
2025-07-16 reference container
2025-07-16 add docker to changelog
2025-07-16 Add dockerfiles for building SDRR more easily (#5)
2025-07-17 get no_std working
2025-07-19 first implementation of banked roms
2025-07-19 first implementation of bank switching
2025-07-19 improve error message
2025-07-19 support bank switched sets
2025-07-19 fix up sdrr-info for bank switching
2025-07-19 add 1541 bank config
2025-07-19 add bank switching support to test
2025-07-19 better test output
2025-07-19 add bank-1541
2025-07-19 add char rom bank switched sets
2025-07-19 add bank switching
2025-07-19 avoid prebuilding bank images for now
2025-07-19 Adds dynamically bank switched ROMs (#6)
2025-07-21 add demo programs
2025-07-21 better formatting
2025-07-21 fix f401rb/rc
2025-07-21 commit new fun char set roms
2025-07-21 improve ci triggering
2025-07-21 make ci more resilient
2025-07-21 improve configs
2025-07-21 slow down demos
2025-07-21 initial implementation
2025-07-21 get c main loop working
2025-07-21 add to ci
2025-07-21 comment register use
2025-07-21 add vic-20 ntsc config
2025-07-21 improve demos
2025-07-22 add demo docs
2025-07-22 update release instructions
2025-07-22 prepare sdrr-fw-parser for publishing to crates.io
2025-07-22 prep sdrr-fw-parser for publishing
2025-07-22 update release process
2025-07-22 move release notes
2025-07-25 Added config files for ti99/4a and the coco 2
2025-07-27 Add TI-99/4a and CoCo2 configs
2025-07-27 add compatibiltiy info
2025-07-28 fw-parser refactoring for airfrog integration
2025-07-29 refactor sdrr-gen and store off files used to build ROM
2025-07-29 add dumb c impl
2025-07-29 fix compile error
2025-07-29 tweak c main loop
2025-07-29 add c main loop
2025-07-29 try some fixes
2025-07-29 update info on RP2350
2025-07-30 move sdrr-fw-parser and sdrr-info to async
2025-07-31 update sdrr-fw-parser for airfrog integration
2025-07-31 have served byte counting working
2025-08-01 add additional runtime variables
2025-08-01 expose rom table length
2025-08-02 change defaults, most rev f to verified, add rev f2
2025-08-02 added sdrr-check
2025-08-10 mostly cargo fmt and other refactoring
2025-08-10 add lookup raw range
2025-08-10 added new basic demo
2025-08-11 fix ram_rom_image location
2025-08-11 Add new BASIC demo prog
2025-08-11 remove extraneous eprintln
2025-08-12 test no rom access counting
2025-08-12 update version numbering
2025-08-12 reserve large space for main loop
2025-08-12 Release v0.3.0 (#10)
    * fw-parser refactoring for airfrog integration
    * refactor sdrr-gen and store off files used to build ROM
    * move sdrr-fw-parser and sdrr-info to async
    * update sdrr-fw-parser for airfrog integration
    * have served byte counting working
    * add additional runtime variables
2025-08-12 document how to get bin file
2025-08-12 Have main loop executing from RAM successfully
2025-08-12 had wrong latency masks
2025-08-12 nope they were per the rm
2025-08-13 f2 verified
2025-08-13 add to clones docs
2025-08-13 support F405 CCM RAM
2025-08-13 COUNT_ROM_ACCESS and C_MAIN_LOOP not compatible
2025-08-13 allow more aggressive overclocking
2025-08-15 add rev g1
2025-08-15 verified with F446RC
2025-08-16 more pcb maintenance
2025-08-16 rename
2025-08-16 add hw rev g1
2025-08-16 improve v0.3.1 changelog
2025-08-16 increment version number
2025-08-16 fix typo
2025-08-16 clarify branch behaviour
2025-08-16 Release v0.3.1 (#14)
    * try some fixes
    * Have main loop executing from RAM successfully
    * had wrong latency masks
    * nope they were per the rm
    * f2 verified
    * add to clones docs
2025-08-16 Add basic RP2350 implementation - no GPIO support
2025-08-16 get rp2350 booting
2025-08-16 Release v0.3.1 (#15)
    * try some fixes
    * Have main loop executing from RAM successfully
    * had wrong latency masks
    * nope they were per the rm
    * f2 verified
    * add to clones docs
2025-08-16 clarify boot block
2025-08-16 more progress with RP2350
2025-08-17 let sel pins work either way
2025-08-17 rebuilt image select behavior
2025-08-17 finish rp235x support in main_loop()
2025-08-17 major refactoring of main_loop to support rp2350
2025-08-17 update sdrr-gen to generate 64KB images for RP235x always
2025-08-17 remove duplication and improve comment
2025-08-17 improve test
2025-08-17 get test running on stm32f4
2025-08-17 get tests working for rp2350 images
2025-08-17 add hardware rev g
2025-08-17 add rp2350 tests and fix up ci
2025-08-17 fix out by 1 errors
2025-08-17 fix unused variables
2025-08-17 fix DEBUG_LOGGING
2025-08-17 get rid of left behind #defines
2025-08-17 fix COUNT_ROM_ACCESS/C_MAIN_LOOP combo
2025-08-17 correct handle bank switched images when X1/X2 configurable
2025-08-18 improve checking
2025-08-18 default has changed now
2025-08-18 define proper defaulg
2025-08-19 fix STM32 with no X pins - single ROM image
2025-08-19 validated existing STM32 single ROM, bank switching and multi-rom set operation with refactored code
2025-08-19 tidy up rp2350 support
2025-08-19 preload ram image on rp2350 to dedicatd 64KB SRAM bank
2025-08-19 div MCO by 5, not 4
2025-08-19 allow overclocking above 400MHz
2025-08-19 correct PLL div
2025-08-19 correct latency mask
2025-08-21 v0.4.0 fw parser updates
2025-08-21 add clone info
2025-08-21 fix MAIN_LOOP_ONE_SHOT
2025-08-21 get rp2350 board working :-)
2025-08-21 add xip cache pinning of main loop
2025-08-22 move to xip cache warming
2025-08-22 add ADC and overclocking to RP2350
2025-08-22 tweak rp2350 clocking
2025-08-22 update docs for RP2350
2025-08-22 add delay so overclocking boots without DEBUG logging
2025-08-23 improve RP2350 doc
2025-08-23 add RP2350 co-processor support
2025-08-23 add gpioc
2025-08-23 correct bank handling when jumpers pull to gnd
2025-08-23 first version of onerom pi asm demo
2025-08-23 get one rom asm program working
2025-08-23 make border black
2025-08-23 improve screen 1
2025-08-24 add rp2350 fab files
2025-08-24 remove new ff8192 test rom from test-sdrr as it makes the image too big for the smallest F401s
2025-08-25 add VIC-20 RP2350 issue
2025-08-25 correctly handle X1/X2 being pulled low by jumpers
2025-08-25 add rp2350 to ci
2025-08-25 Release v0.4.0 including RP2350 support (#13) (#17)
    * had wrong latency masks
    * nope they were per the rm
    * support F405 CCM RAM
    * allow more aggressive overclocking
    * add hw rev g1
    * improve v0.3.1 changelog
2025-08-25 correct doc about which RP2350 hw revs are 5v tolerant
2025-08-25 reduce severity of vos not ready
2025-08-25 uprev main to 0.4.1
2025-08-25 fix #11 - don't allow STATUS_LED=1 on hw without status LED
2025-08-25 fix breaking rev d and status led tests
2025-08-25 include RP2350 in release
2025-08-25 add erratum e9 info
2025-08-25 Add RP2350 build commands to README.md and generally update the docs to refer to One ROM/RP2350

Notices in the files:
rust/sdrr-info/src/main.rs:
MIT License
